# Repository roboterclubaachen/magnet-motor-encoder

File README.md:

# magnet-motor-encoder

## board-as5045b_rev10

### Motorencoder für axial befestigten diametralen Magneten

Motor-Encoder mit ams AS5045B.

Der AS5045B ist ein IC welcher die Ausrichtung eines über ihm befindlichen Magneten mit 12 Bit Auflösung erfasst.

An der Motorachse muss ein Ø 6 mm x 2.5 mm Magnet mit diametraler Orientierung befestigt werden, die zulässige Toleranz betrögt 0.1 mm.
Das Magnet ist exakt mittig über dem IC (welcher mittig auf der Platine platziert ist) ausgerichtet werden, der Toleranzbereich beträgt hier 0.25mm.

### Mechanische Dimensionen

Alle Angaben in Millimeter.

### Bauteile

Anzahl | Bauteil              | Bezeichnung / MPN
------ | -------------------- | -----------------------
1      | Magnetsensor IC      | AS5045B-ASSM
1      | Stecker Vorderseite  | [JST GH SM05B-GHS](https://www.digikey.de/product-detail/de/jst-sales-america-inc/SM05B-GHS-TB-LF-SN/455-1567-1-ND/807835) (1.25mm)
1      | Stecker Rückseite    | [JST GH BM05B-GHS](https://www.digikey.de/product-detail/de/jst-sales-america-inc/BM05B-GHS-TBT-LF-SN-N/455-1581-1-ND/807849) (1.25mm)
1      | LED Rot              | Bauform 0603
1      | LED Gelb             | Bauform 0603
2      | Vorwiderstand LED    | Bauform 0402
3 or 4 | Null-Ohm-Widerstand  | Bauform 0402
2      | Kondensator          | 2,2µF, >6,3V, X7R, Bauform 0603

### Stecker

Auf der Platine sind zwei 5-polige [JST GH](https://jst.de/product-family/show/89/gh) Stecker vorgesehen, welche Alternative bestückt werden können.
Der Stecker auf Vorderseite der Platine (wo auch der Sensor sitzt) bietet einen horizontalen Kabelausgang während auf der Rückseite ein vertikaler Kabelausgang vorgesehen ist.

Das Pinout beider Stecker ist identisch.

Pin | ABI-Interface | Serielles Interface
--- | ------------- | -------------------
 1  | A             | Data Out
 2  | +5V oder +3V3 | +5V oder +3V3
 3  | B             | Clock
 4  | I             | Chip Select (inverted)
 5  | GND           | GND

### Optionen / Konfiguration

#### Versorgungsspannung

Es sind sowohl 3,3V als auch 5V Versorgungsspannung möglich.
Die Versorgungsspannung muss mittels des einzigen Null-Ohm-Widerstands auf der Vorderseite (Beschriftung "3V") konfiguriert werden.

Spannung     | Null-Ohm-Widerstands (Beschriftung "3V")
------------ | ----------------------------------------
4,5V .. 5,5V | Nicht bestückt
3,0V .. 3,6V | Bestückt

#### Interface

Mittels Null-Ohm-Widerständen können wahlweise das ABI- oder das serielle Interface aktiviert werden.

Zur Nutzung des ABI-Interfaces müssen die drei Null-Ohm-Widerstände innerhalb der blauen Markierung eingelötet werden.

Zur Aktivierung des seriellen Interfaces müssen die drei Null-Ohm-Widerstände innerhalb der roten Markierung eingelötet werden.

### Diagnose LEDs
* Rote und gelbe LEDs: Magnetfeldstärke
  * Aus: optimaler Betrieb
  * Gelb leuchtet: schwache Magnetfeldstärke, Magnet näher an IC platzieren.
  * Rot leuchtet: starke Magnetfeldstärke, Magnet weiter vom IC entfernt platzieren.
  * Rot und Gelb leuchten gleichzeitig: zu starkes oder zu schwaches Magnetfeld, keine zuverlässiger Betrieb möglich.

## board-as5045b

### Motorencoder für axial befestigten diametralen Magneten

Siehe [oben](#board-as5045b_rev10).

Die Platine ist hat exakt 22mm Durchmesser und sollte damit zu den *Namika* Motoren (ebenfalls 22mm Durchmesser) passen.
Das Magnet ist exakt mittig über dem IC, welcher mittig auf der Platine platziert ist, ausgerichtet werden.

### Diagnose LEDs
* Blaue LED: Power
* Rote und gelbe LEDs: Magnetfeldstärke
  * Aus: optimaler Betrieb
  * Gelb leuchtet: schwache Magnetfeldstärke, Magnet näher an IC platzieren.
  * Rot und Gelb leuchten: zu starkes oder zu schwaches Magnetfeld, keine zuverlässiger Betrieb möglich.

## board-as5304

### Motorencoder für axial befestigten mehrpoligen Ringmagneten

Motor-Encoder mit **ams** AS5304(A).

Der AS5304 ist ein IC welcher die Bewegung eines über ihm befindlichen mehrpoligen Magneten mit 160 Schritten pro Magnetpolpaar erfasst.
Die Platine ist hat etwa 12 mm Höhe und 39 mm Breite sowie ein 2mm Loch zu Ausrichtung über der Motorwelle.
Bei Bedarf kann dieses Loch aufgebohrt werden, in der Umgebung sind keine Leiterbahnen und kein Kupfer vorhanden.

An der Motorachse muss ein Ringmagnet mit 24 mm Innendurchmesser und 32 mm Außendurchmesser (-> MIttendurchmesser 28 mm) mittels eines nicht ferromagmetischen Werkstoffs befestigt werden.
Das Sensorarray im IC befindet sich exakt 28 mm vom Loch für die Motorachse entfernt, sodass die Platine bei Verwendung des oben genannten Magneten nur an der Motorachse und mit ca. 0.5 mm zum Ringmagnet ausgerichtet werden muss.

### Diagnose
* Blaue LED: Power
* Am Testpoint **AO** kann eine von der Magnetfeldstärke abhängige Spannung (gegen Testpoint **GND**) gemessen werden.

## License

Copyright Raphael Lehmann 2016-2019

Licensed under CERN OHL v.1.2

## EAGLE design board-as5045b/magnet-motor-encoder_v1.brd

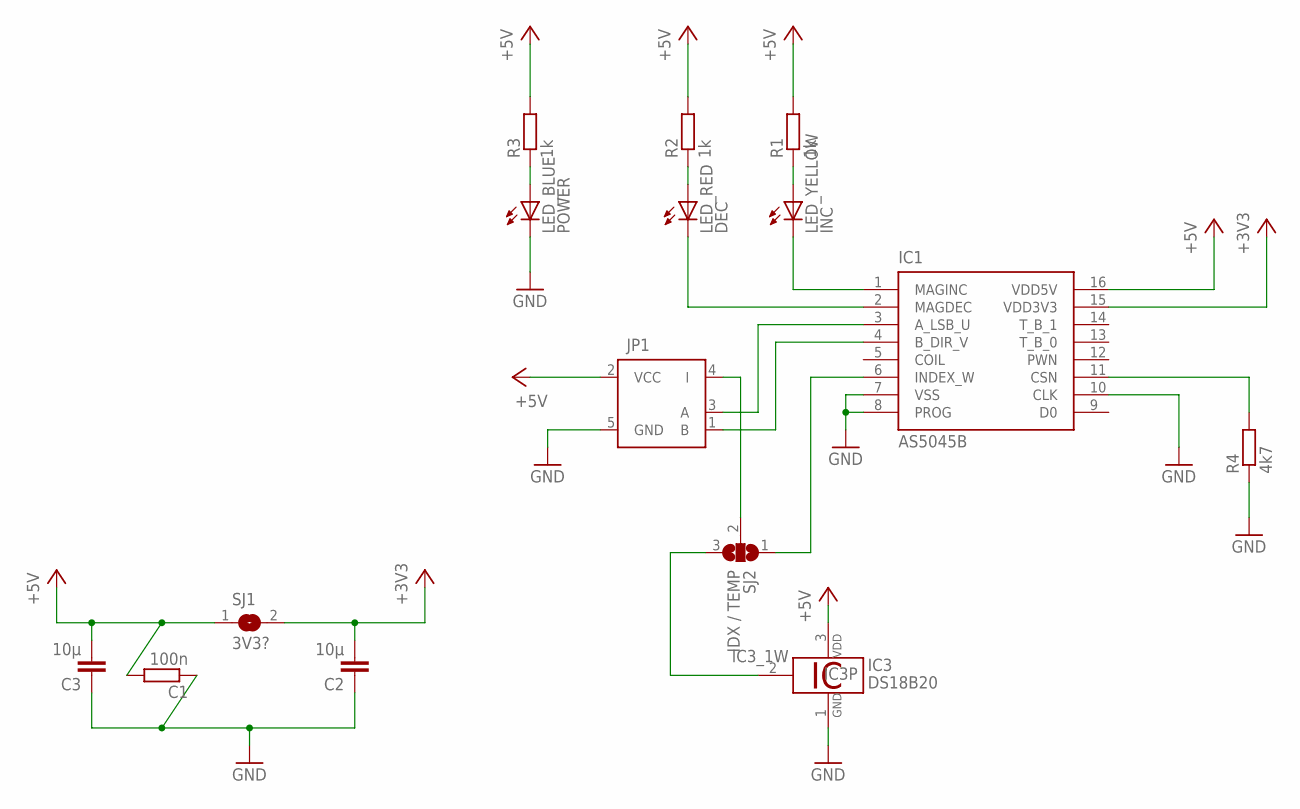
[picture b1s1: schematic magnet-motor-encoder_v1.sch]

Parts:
C1: 100n; R0603
C2, C3: 10µ; C0805K
IC1: AS5045B; SSOP16
IC3: DS18B20; TO92-
JP1: ENCODERPSS; 22-23-2051
LED_BLUE: POWER; CHIPLED_0805
LED_RED: DEC; CHIPLED_0805
LED_YELLOW: INC; CHIPLED_0805
R1, R2, R3: 1k; R0805
R4: 4k7; R0805
SJ1: 3V3?; SJS
SJ2: IDX / TEMP; SJ_2

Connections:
+3V3: C2.2, IC1.15 (VDD3V3), SJ1.2
+5V: C1.2, C3.2, IC1.16 (VDD5V), IC3.3 (VDD), JP1.2 (VCC), R1.2, R2.2, R3.2, SJ1.1
A: IC1.3 (A_LSB_U), JP1.3 (A)
B: IC1.4 (B_DIR_V), JP1.1 (B)
GND: C1.1, C2.1, C3.1, IC1.7 (VSS), IC1.8 (PROG), IC1.10 (CLK), IC3.1 (GND), JP1.5 (GND), LED_BLUE.C, R4.1
LED_RED: IC1.2 (MAGDEC), LED_RED.C
LED_YELLOW: IC1.1 (MAGINC), LED_YELLOW.C
unnamed: JP1.4 (I), SJ2.2
unnamed: IC1.6 (INDEX_W), SJ2.1
unnamed: IC3.2 (1W), SJ2.3
unnamed: IC1.11 (CSN), R4.2
R_LED_BLUE: LED_BLUE.A, R3.1
R_LED_RED: LED_RED.A, R2.1
R_LED_YELLOW: LED_YELLOW.A, R1.1

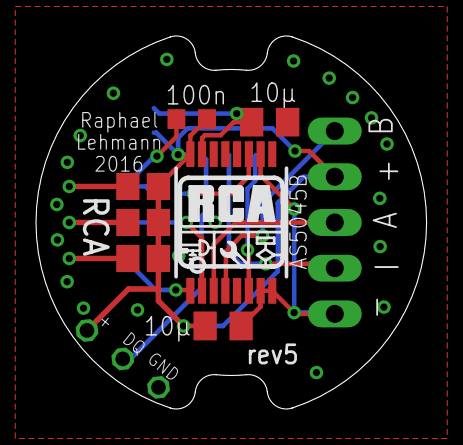
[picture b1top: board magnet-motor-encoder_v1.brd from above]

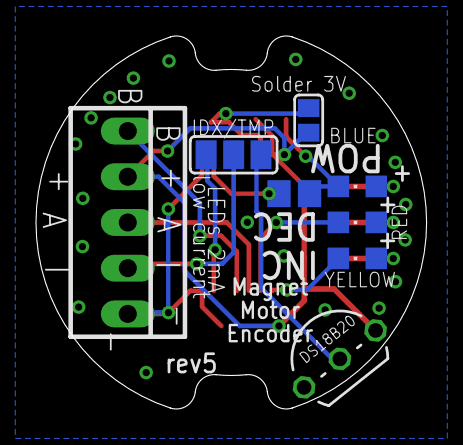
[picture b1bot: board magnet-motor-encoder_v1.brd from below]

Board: 2 copper layers, 21.7 x 20.7 mm, 16 parts (8 on the bottom side), 14 nets.

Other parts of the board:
U$1: LOGO_SILK

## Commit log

2016-07-04 add gitignore
2016-07-04 inital board schematic and layout
2016-07-04 board layout and silkscreen
2016-07-04 board: silkscreen and ground vias
2016-07-04 board; adjust silkscreen
2016-07-04 add README
2016-07-06 board: add 1wire eagle library (LGPL)
2016-07-06 board: add DS18B20 temperature sensor (optional/uses encoder index pin signal)
2016-07-06 board: adjust silk screen; add rev2 label
2016-07-06 board: some minor fixes and improvements; rev3 label
2016-07-09 added magnet-motor-encoder-as5304 schematic (kicad) and kicad libs for solder jumper, as5304 and rca encoder psk
2016-07-09 remove kicad lib cache / extend gitignore
2016-07-09 board as5304: add AO and GND test points
2016-07-10 board AS5304: add Power LED
2016-07-10 KiCad lib solder jumper: Pins changed to passive
2016-07-10 board as5304: modified solder jumper; ERC passed
2016-07-10 kicad lib: add open-project kicad footprint lib
2016-07-10 board as5304: footprints selected, netlist created
2016-07-10 board as5304: add test point library; replace measurement point footprint
2016-07-10 board as5304: add lib bjh-kicad-mountingholes-fp
2016-07-10 board as5304: create pcb layout
2016-07-10 board as5304: remove generated netlist file
2016-07-10 board as5304: replaced absolute libary paths
2016-07-10 board as5304: named signals in schematic
2016-07-10 board as5304: fix component values
2016-07-10 board as5304: finish pcb layout and silkscreen
2016-07-10 board as5045b: integrate mounting holes in board outline
2016-07-10 renamed board directories
2016-07-10 add as5304 board and images to README
2016-07-26 board as5304: rearrange components
2016-07-31 board as5304: replace bjh-kicad-mountingholes-fp with own fork
2016-07-31 board as5304: finish pcb layout and silkscreen for rev_02
2016-07-31 updated documentation for as5304 rev_02
2016-07-31 add CERN OHL v.1.2 license
2016-08-09 board as5304: replace most 0805 Rs and Cs with 0603 packages
2016-08-09 board as5304: update README images
2016-09-01 board as5045b: new board shape (imported from 3d-model/solidworks); rev4 tag
2016-09-01 board as5304: new board shape (imported from 3d-model/solidworks); rev_04 tag
2016-09-20 board as5045b: moved backside resistors; new rev4 tag
2016-10-12 board as5045b: add missing CSn pulldown resistor; new rev5 tag
2019-08-16 Add datasheet PDFs (No longer available on the AMS website)
2019-08-16 Add new board as5045b_rev10
